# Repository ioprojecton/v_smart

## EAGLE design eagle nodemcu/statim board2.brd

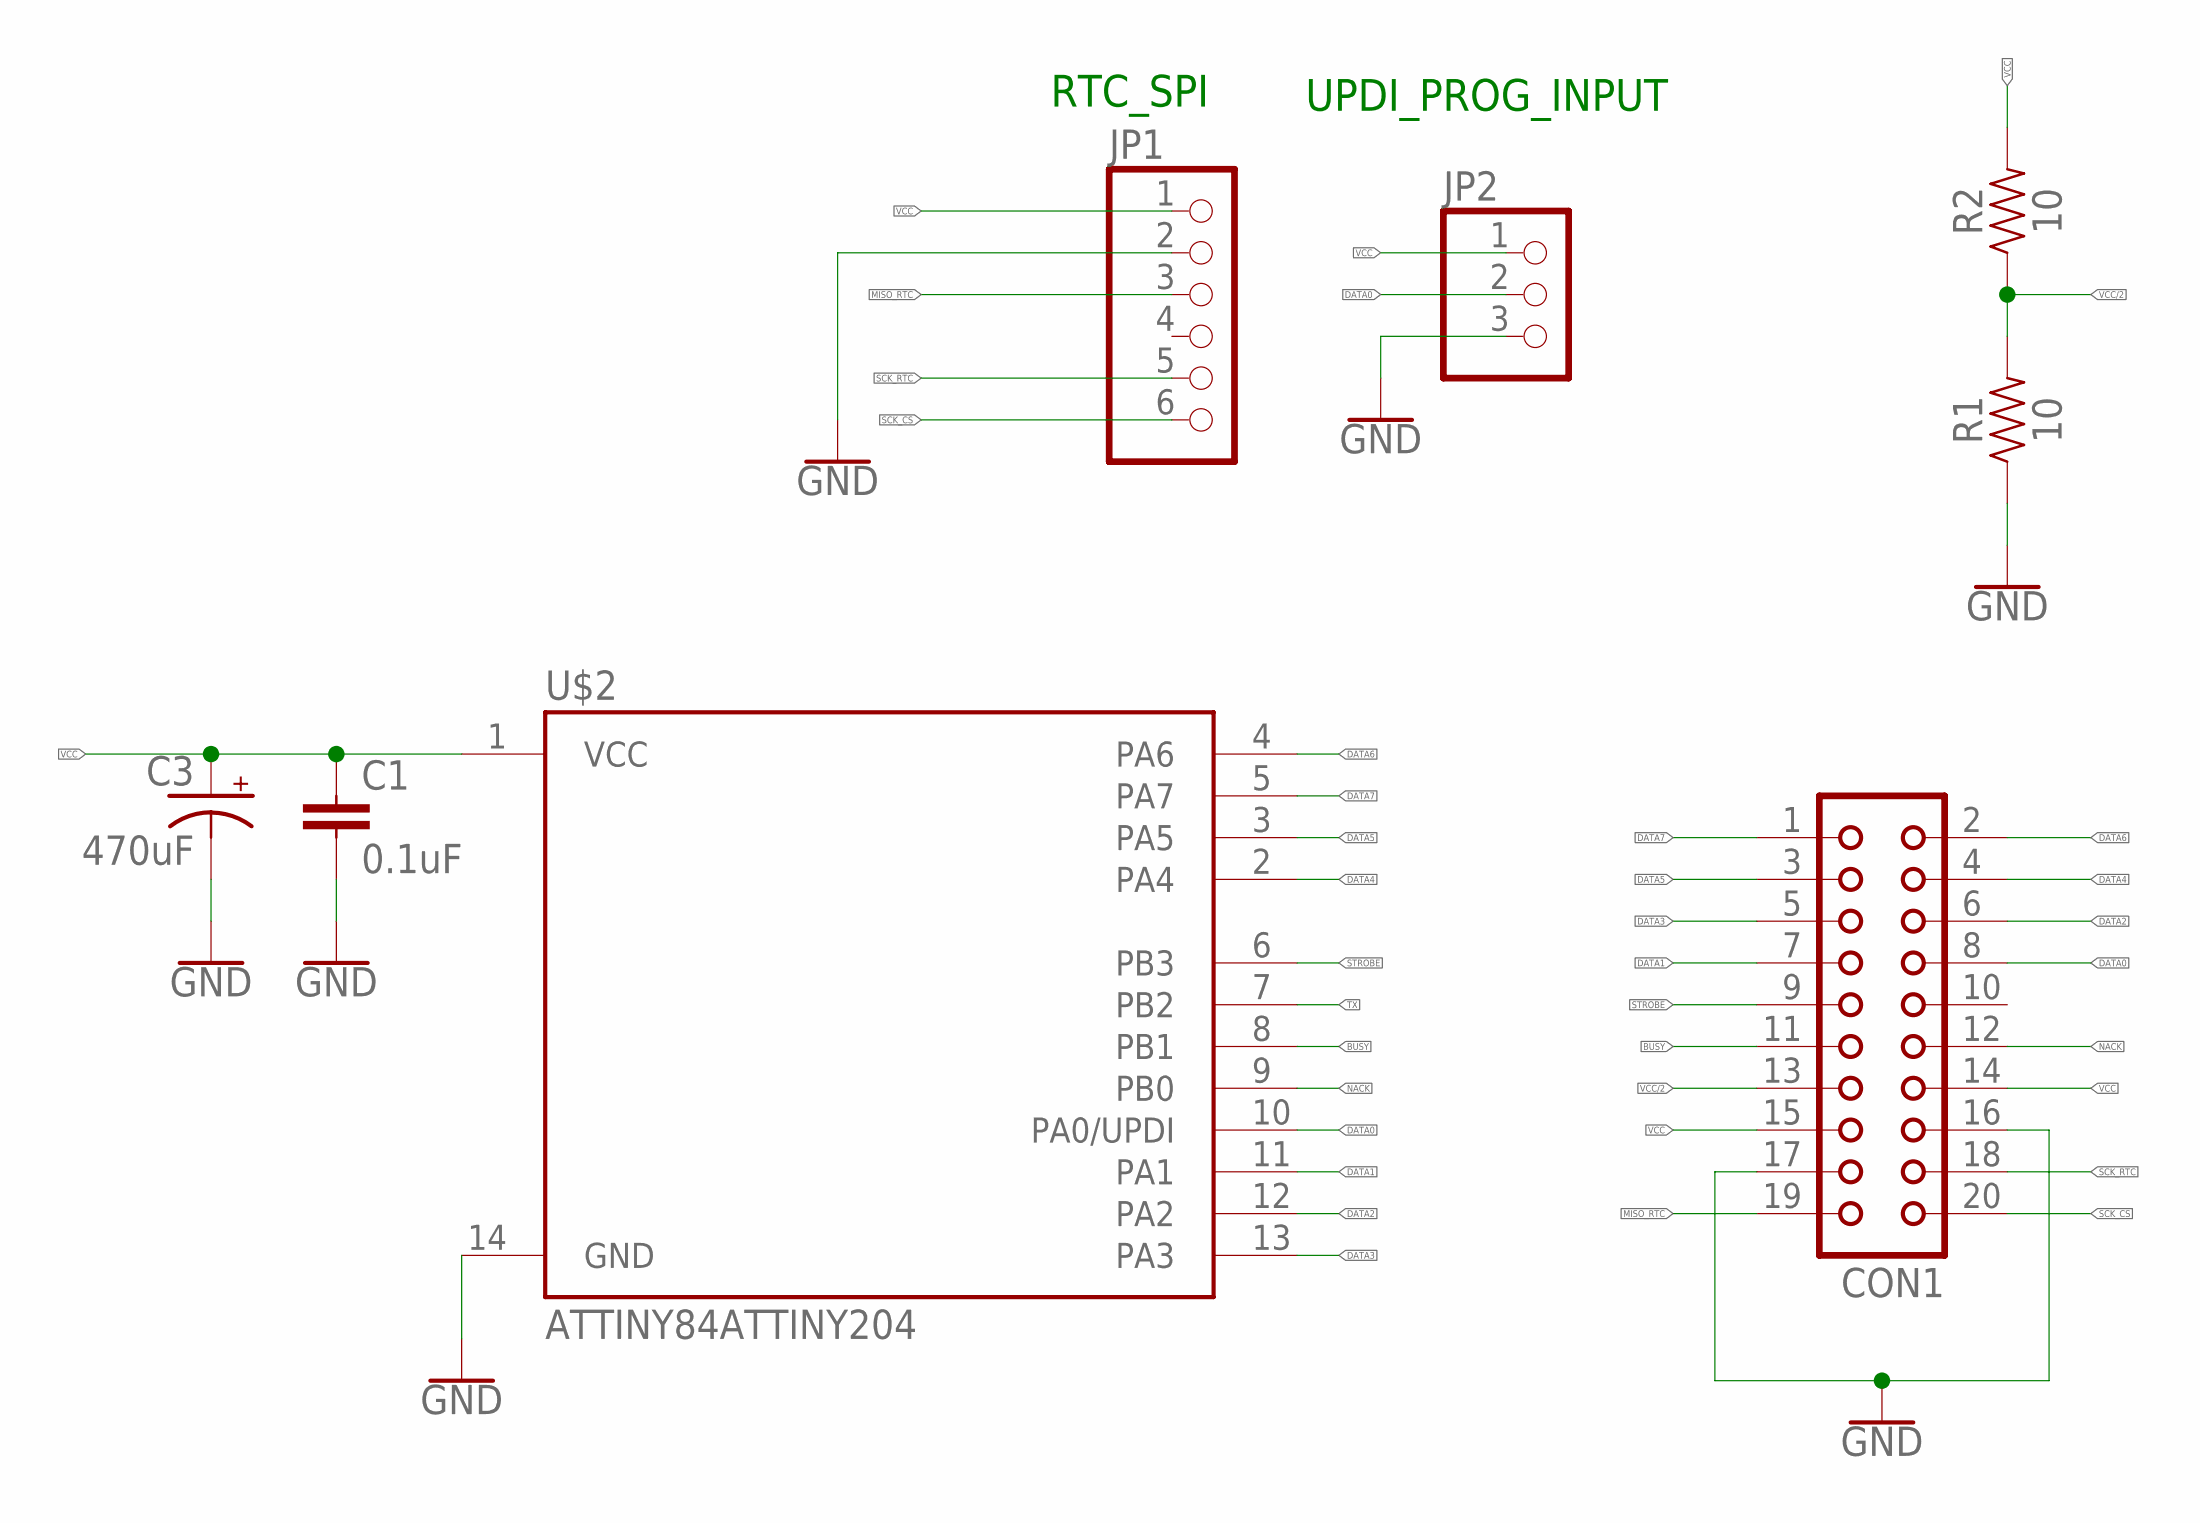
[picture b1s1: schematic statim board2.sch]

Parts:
C1: 0.1uF; 1206
C3: 470uF; PANASONIC_G
CON1: CON20
JP1: PINHD-1X6; 1X06
JP2: PINHD-1X3; 1X03
R1, R2: 10; 1206
U$2: ATTINY84ATTINY204; SO14

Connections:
BUSY: CON1.11, U$2.8 (PB1)
DATA0: CON1.8, JP2.2, U$2.10 (PA0/UPDI)
DATA1: CON1.7, U$2.11 (PA1)
DATA2: CON1.6, U$2.12 (PA2)
DATA3: CON1.5, U$2.13 (PA3)
DATA4: CON1.4, U$2.2 (PA4)
DATA5: CON1.3, U$2.3 (PA5)
DATA6: CON1.2, U$2.4 (PA6)
DATA7: CON1.1, U$2.5 (PA7)
GND: C1.2, C3.-, CON1.16, CON1.17, JP1.2, JP2.3, R1.1, U$2.14 (GND)
MISO_RTC: CON1.19, JP1.3
NACK: CON1.12, U$2.9 (PB0)
SCK_CS: CON1.20, JP1.6
SCK_RTC: CON1.18, JP1.5
STROBE: CON1.9, U$2.6 (PB3)
TX: U$2.7 (PB2)
VCC: C1.1, C3.+, CON1.14, CON1.15, JP1.1, JP2.1, R2.2, U$2.1 (VCC)
VCC/2: CON1.13, R1.2, R2.1

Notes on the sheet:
RTC_SPI
UPDI_PROG_INPUT

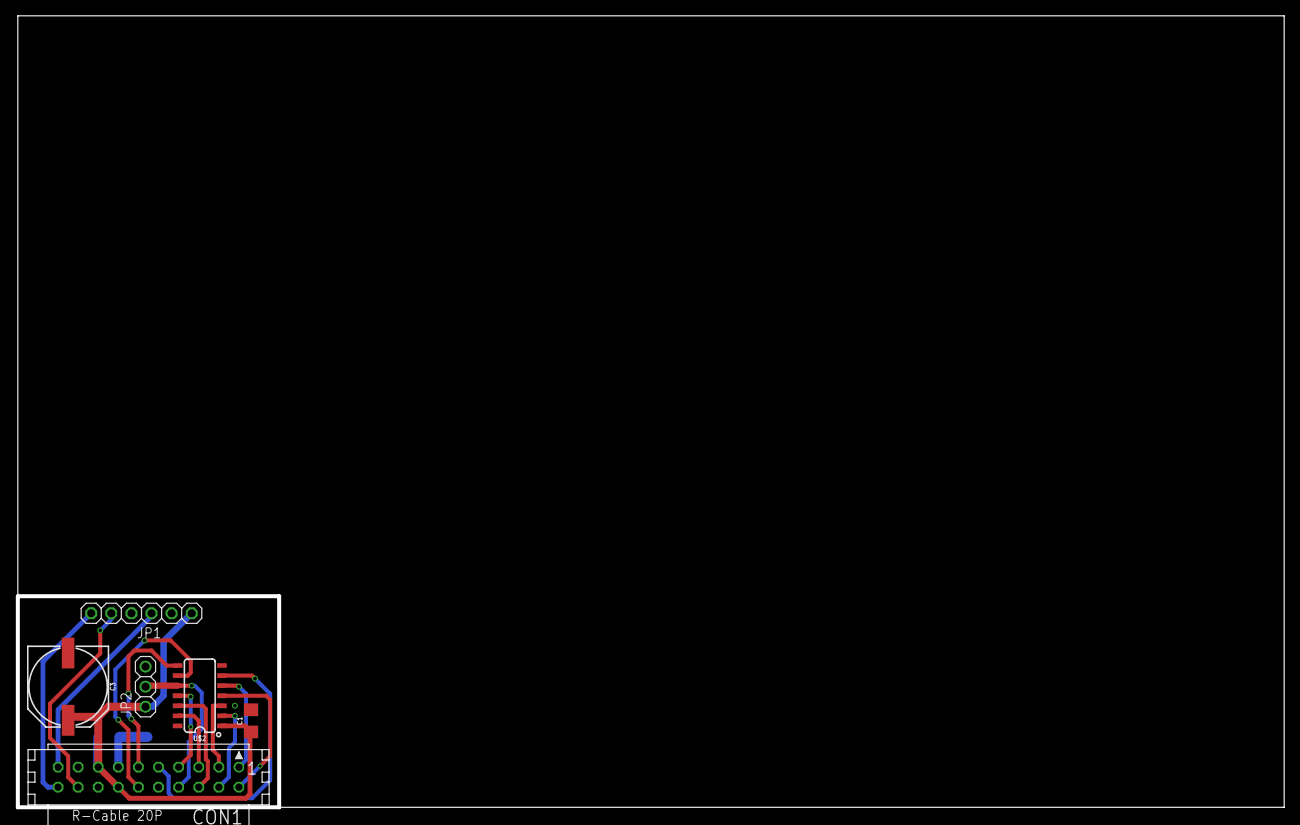
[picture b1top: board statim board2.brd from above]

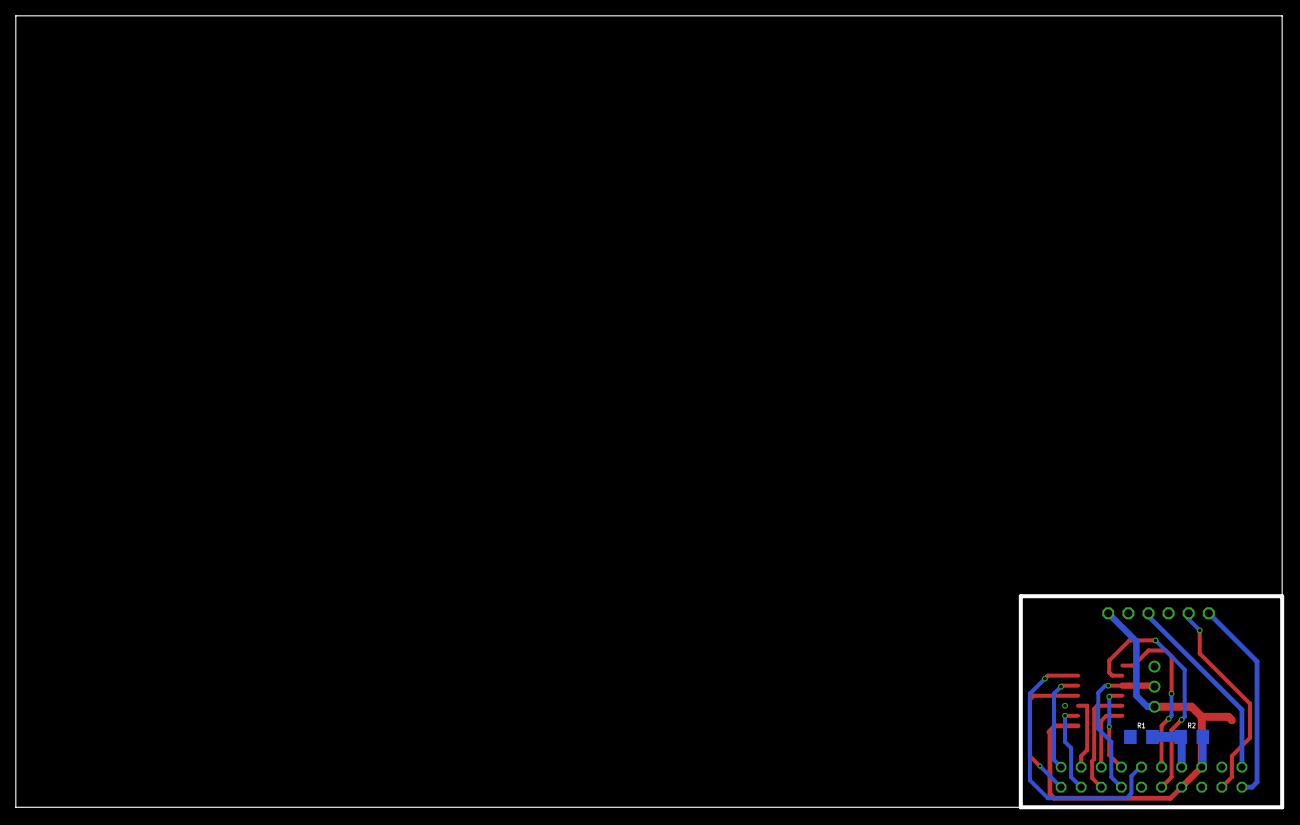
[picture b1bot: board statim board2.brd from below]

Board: 2 copper layers, 160.0 x 100.0 mm, 8 parts (2 on the bottom side), 17 nets.

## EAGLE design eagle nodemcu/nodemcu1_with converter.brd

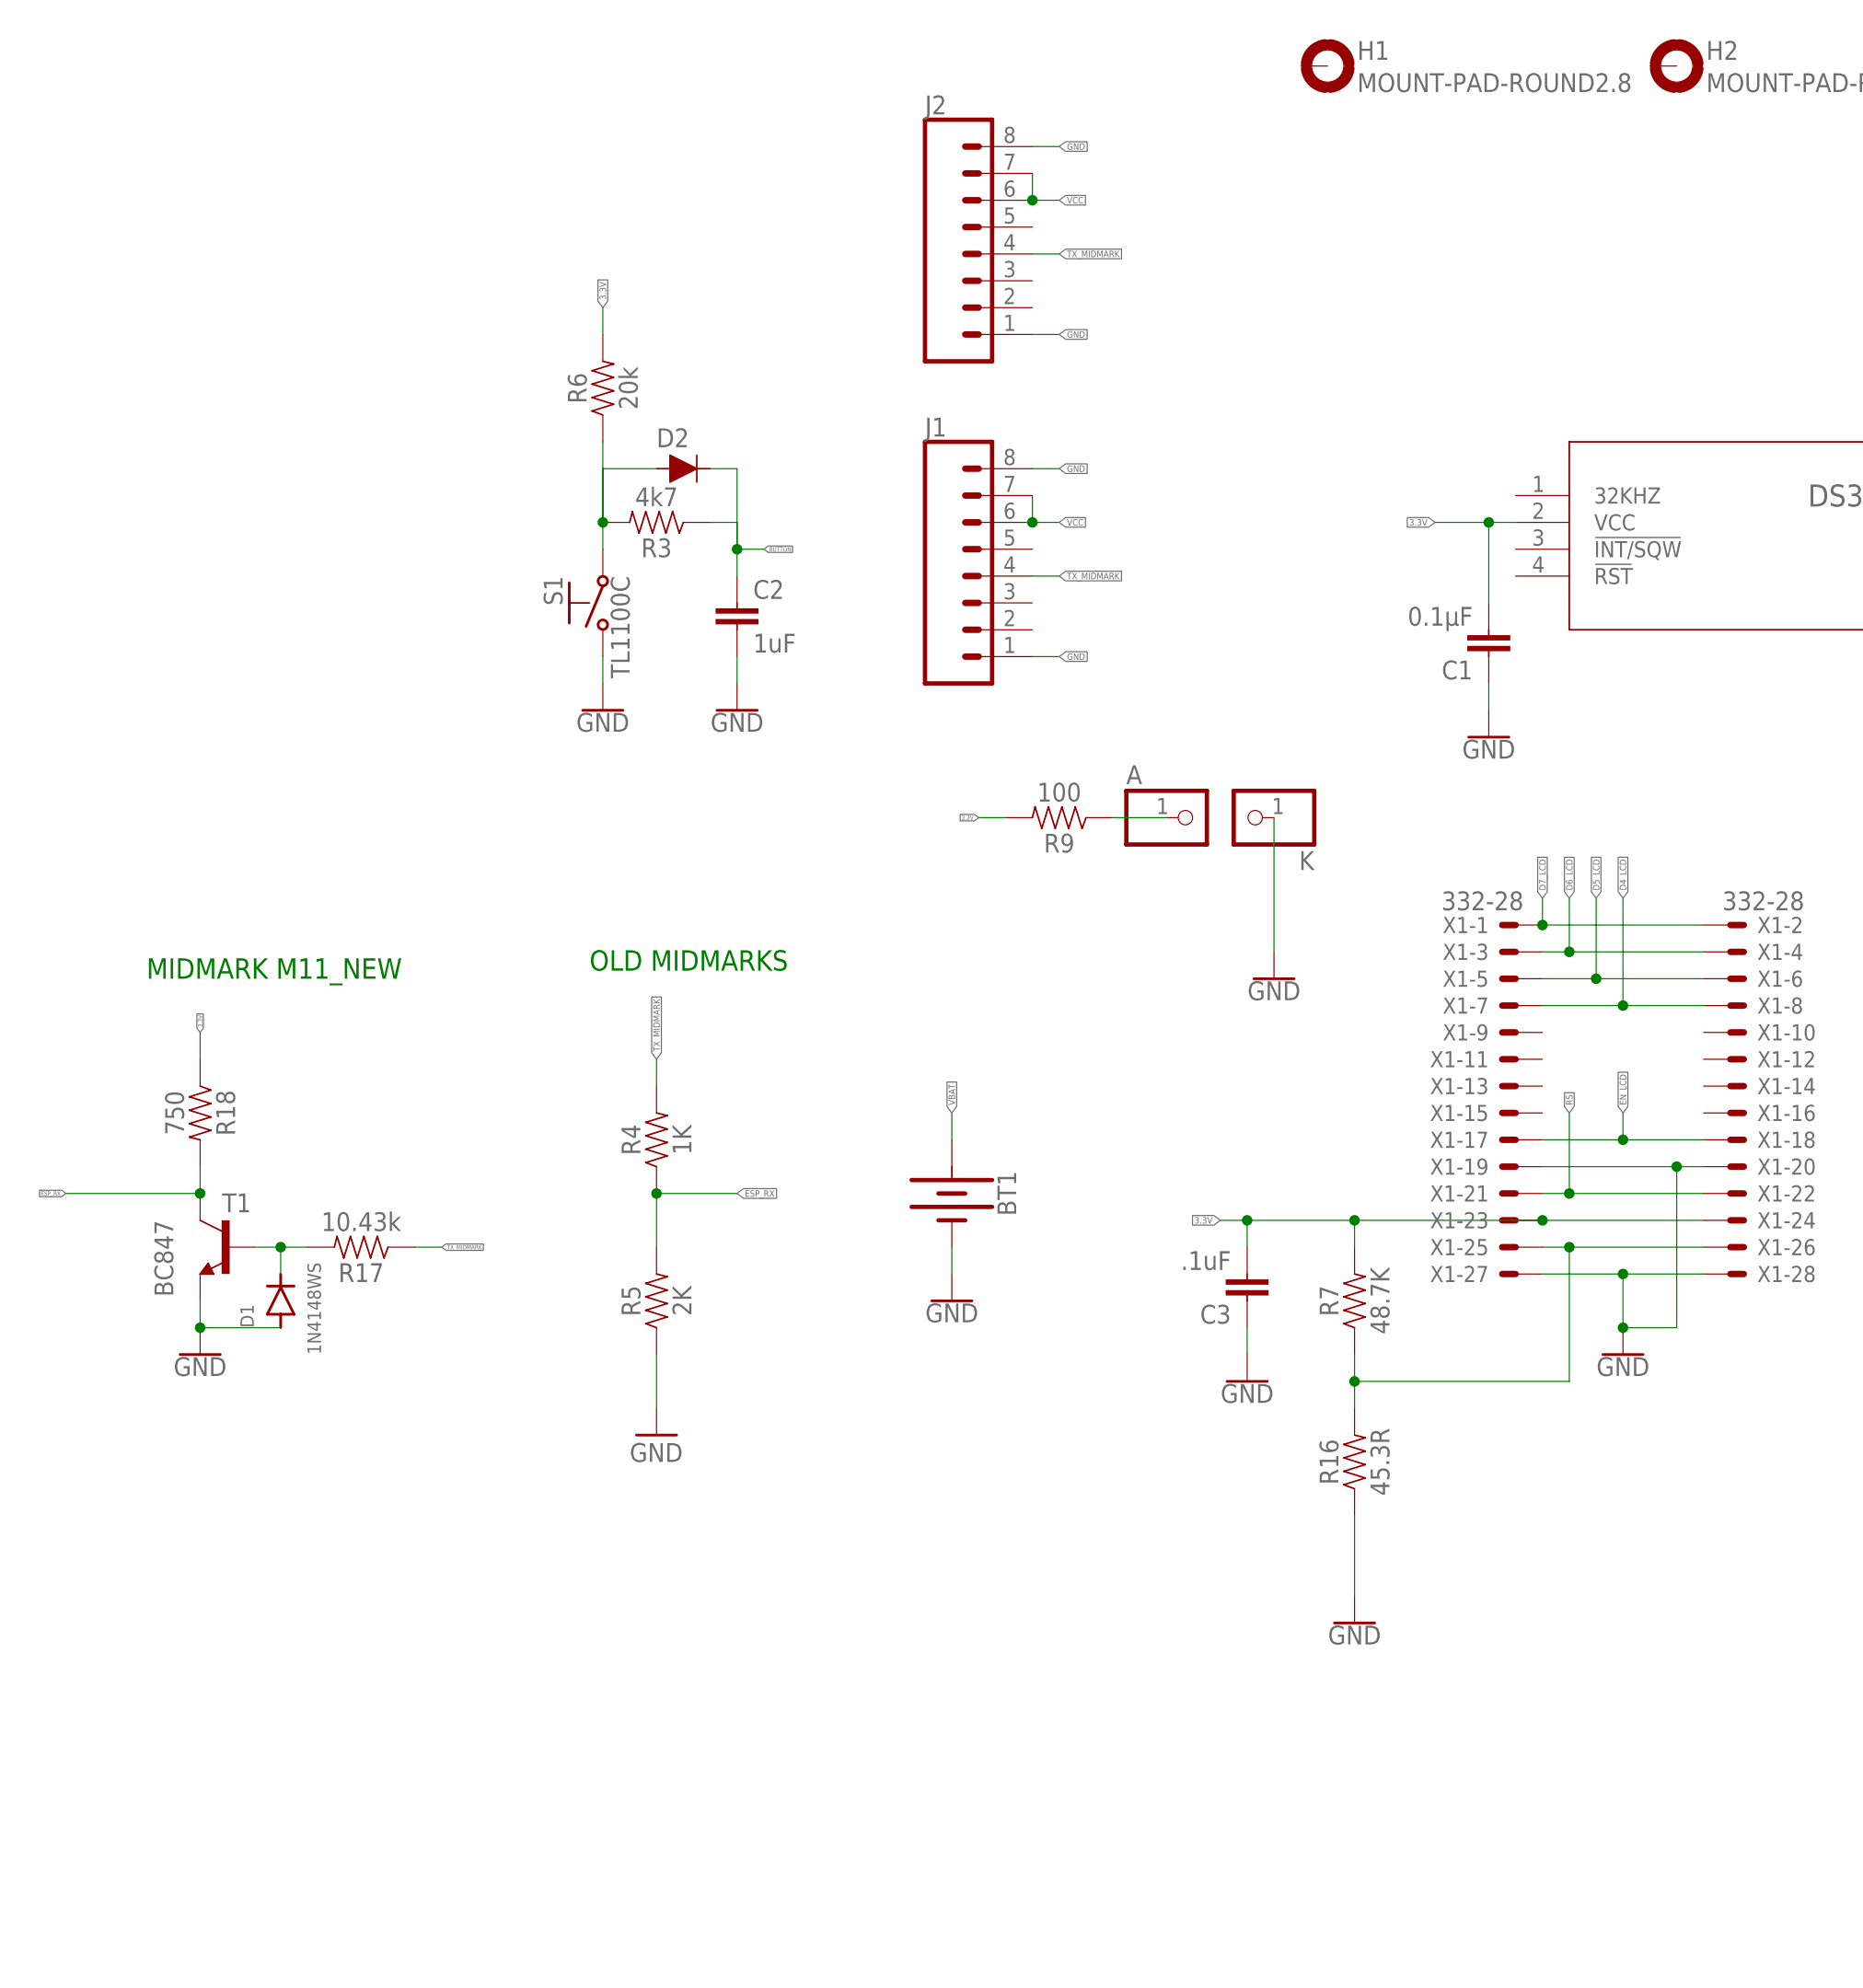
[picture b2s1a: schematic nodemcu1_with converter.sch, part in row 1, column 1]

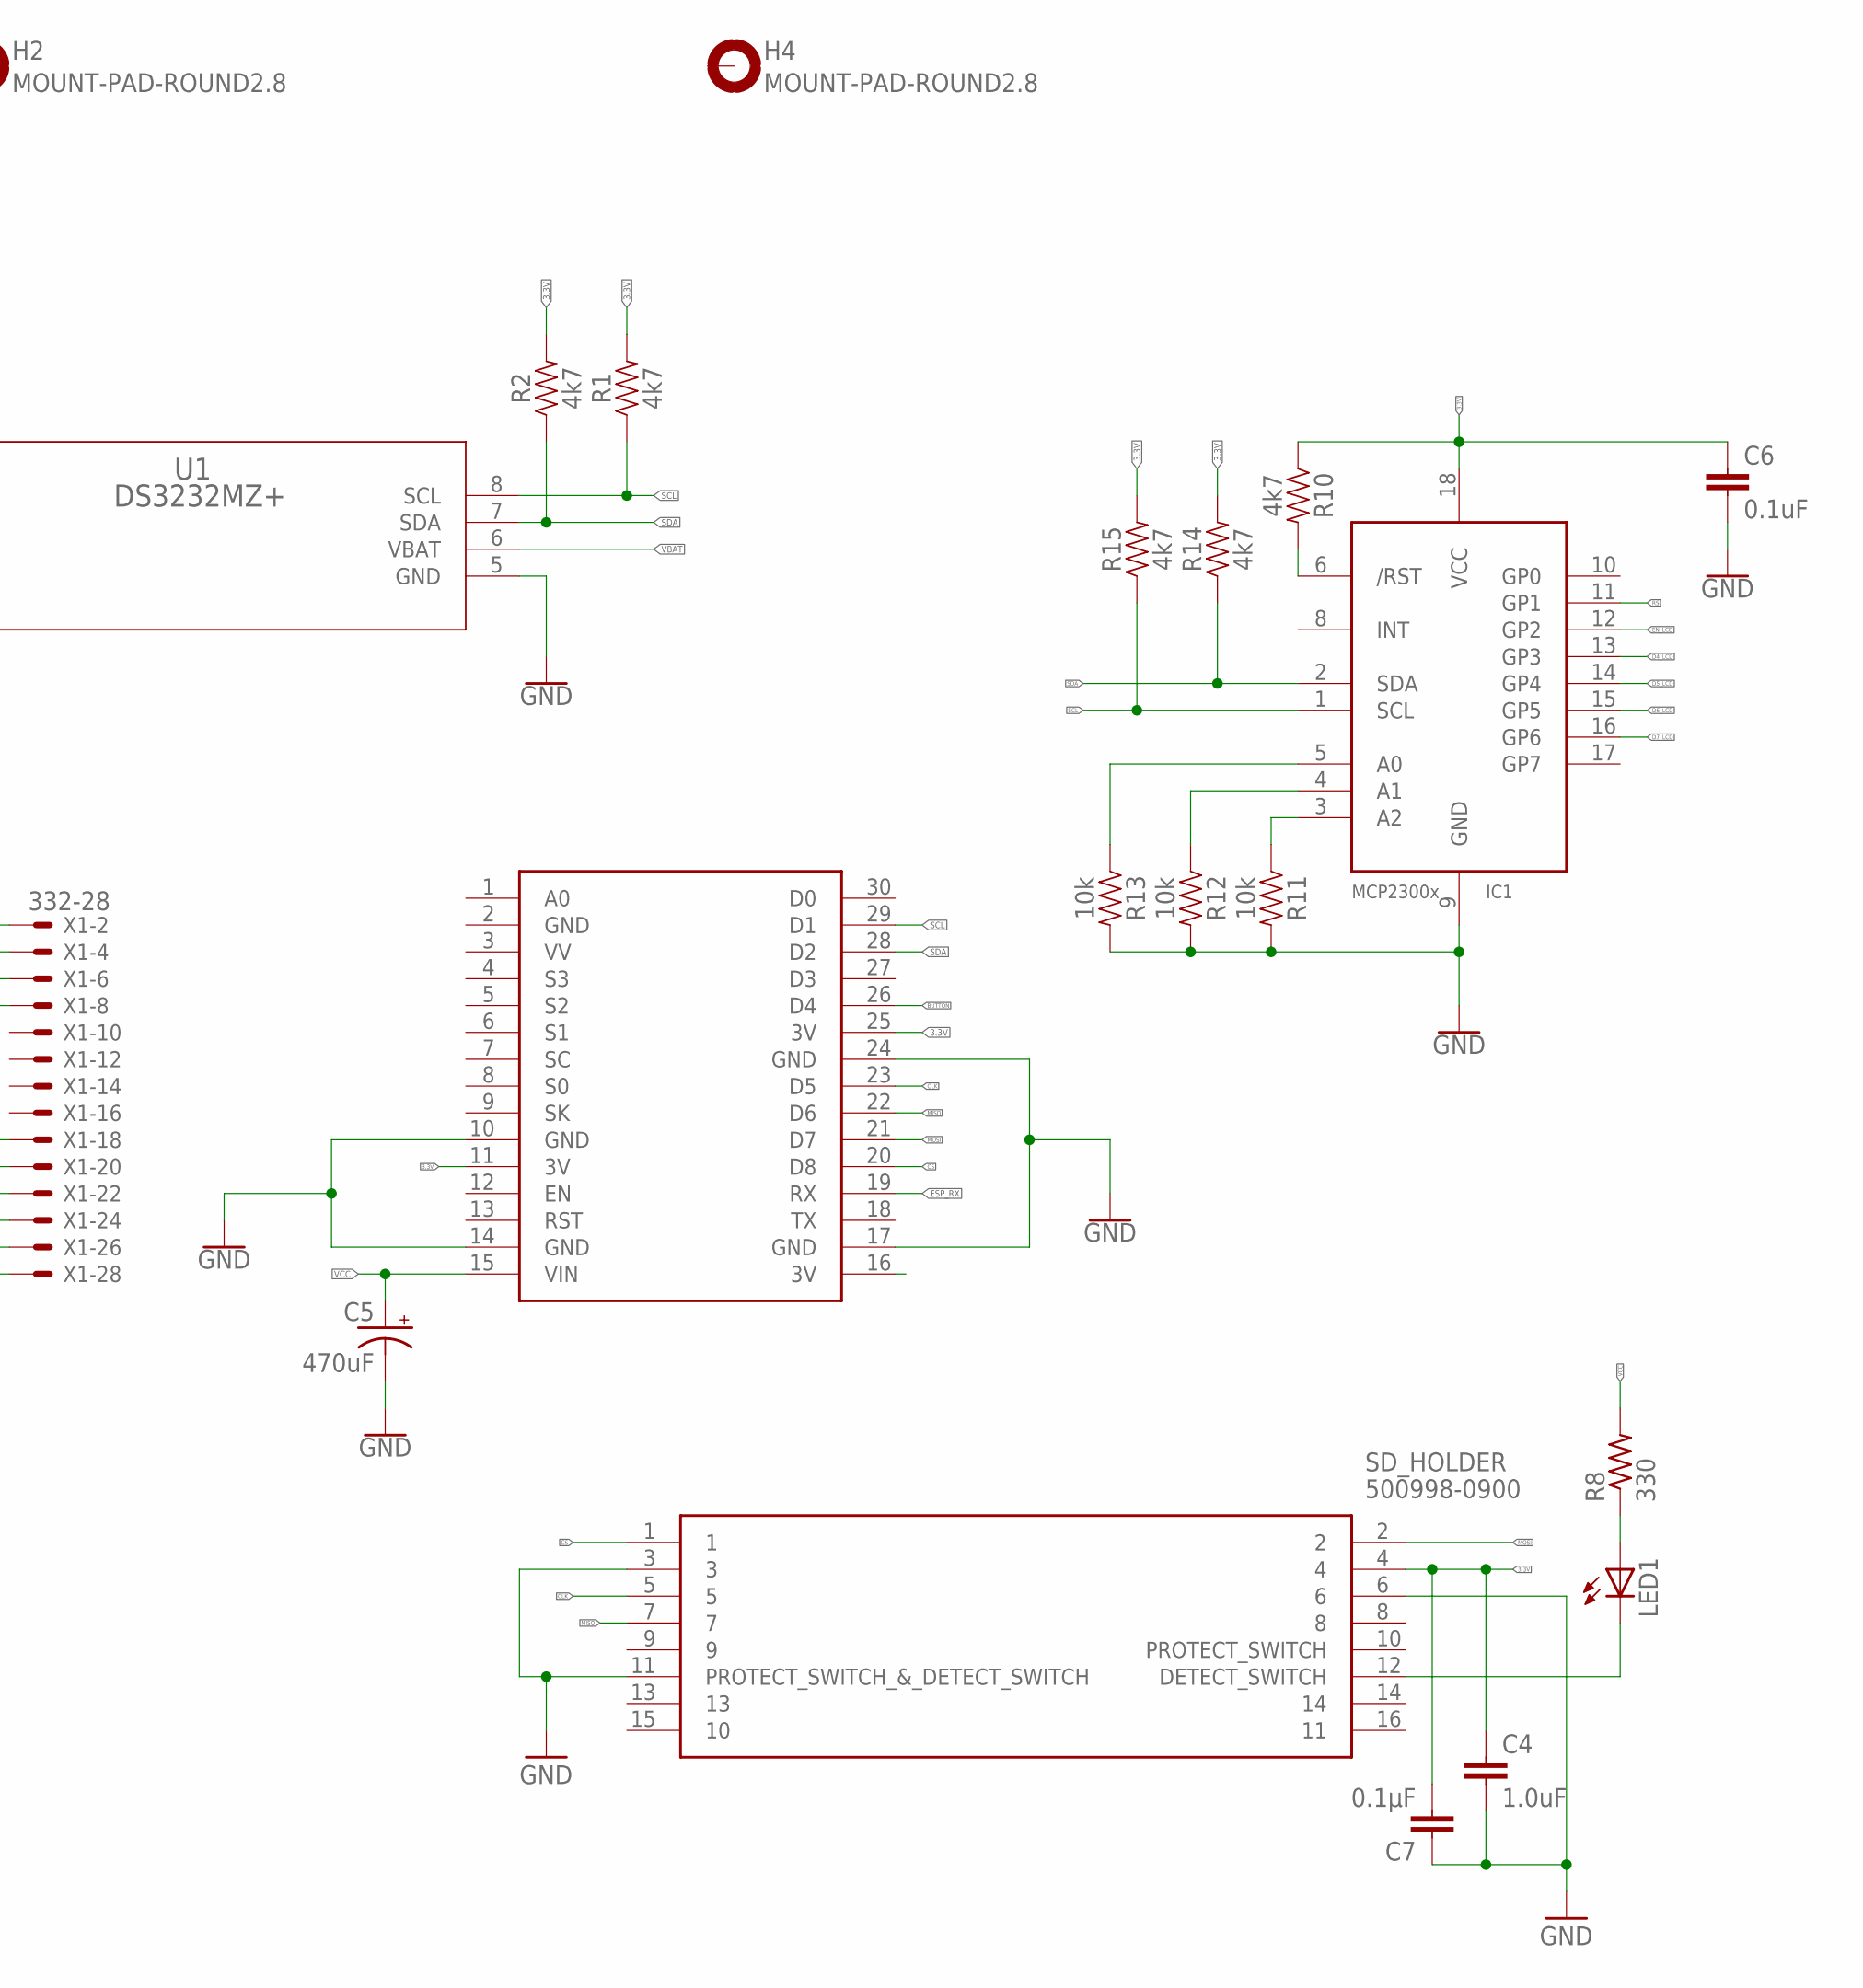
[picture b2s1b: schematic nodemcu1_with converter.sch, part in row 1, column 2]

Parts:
A: PINHD-1X1; 1X01
BT1: BATTERY-20MM_PTH; BATTCOM_20MM_PTH
C1, C7: 0.1µF; 0805
C2: 1uF; 0805
C3: .1uF; 0805
C4: 1.0uF; 1206
C5: 470uF; NIC_10X10.5_CAP
C6: 0.1uF; 0805
D1: 1N4148WS; SOD-323
D2: 1A/50V/1.1V; DIODE-1N4001
H1, H2, H4: MOUNT-PAD-ROUND2.8; 2,8-PAD
IC1: MCP23008/P; DIL18
J1, J2: CONN_08"; 1X08
K: PINHD-1X1; 1X01
LED1: LEDSIDELED; OSRAM-SIDELED
R1, R2, R3, R10, R14, R15: 4k7; 0805
R4: 1K; 0805
R5: 2K; 0805
R6: 20k; 0805
R7: 48.7K; 0805
R8: 330; R0805
R9: 100; 0805
R11, R12, R13: 10k; 0805
R16: 45.3R; 0805
R17: 10.43k; 0805
R18: 750; 0805
S1: TL1100C
SD_HOLDER: 500998-0900; 5009980900
T1: BC847; SOT23
U1: DS3232MZ+; 21-0041B_8
U$1: NODEMCU
X1: 332-28

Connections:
3.3V: C1.2, C3.2, C4.1, C6.1, C7.2, IC1.18 (VCC), R1.2, R2.2, R6.2, R7.2, R9.2, R10.1, R14.2, R15.2, R18.1, SD_HOLDER.4, U1.2 (VCC), U$1.11 (3V), U$1.25 (3V), X1.23, X1.24
BUTTON: C2.1, D2.C, R3.1, U$1.26 (D4)
CLK: SD_HOLDER.5, U$1.23 (D5)
CS: SD_HOLDER.1, U$1.20 (D8)
D4_LCD: IC1.13 (GP3), X1.7, X1.8
D5_LCD: IC1.14 (GP4), X1.5, X1.6
D6_LCD: IC1.15 (GP5), X1.3, X1.4
D7_LCD: IC1.16 (GP6), X1.1, X1.2
EN_LCD: IC1.12 (GP2), X1.17, X1.18
ESP_RX: R4.1, R5.2, R18.2, T1.3 (C), U$1.19 (RX)
GND: BT1.2 (-), C1.1, C2.2, C3.1, C4.2, C5.-, C6.2, C7.1, D1.A, IC1.9 (GND), J1.1, J1.8, J2.1, J2.8, K.1, R5.1, R11.2, R12.2, R13.2, R16.1, S1.2 (S), SD_HOLDER.3, SD_HOLDER.6, SD_HOLDER.11 (PROTECT_SWITCH_&_DETECT_SWITCH), T1.2 (E), U1.5 (GND), U$1.2 (GND), U$1.10 (GND), U$1.14 (GND), U$1.17 (GND), U$1.24 (GND), X1.19, X1.20, X1.27, X1.28
MISO: SD_HOLDER.7, U$1.22 (D6)
MOSI: SD_HOLDER.2, U$1.21 (D7)
unnamed: D2.A, R3.2, R6.1, S1.1
unnamed: A.1, R9.1
unnamed: IC1.6 (/RST), R10.2
unnamed: IC1.3 (A2), R11.1
unnamed: R7.1, R16.2, X1.25, X1.26
unnamed: IC1.4 (A1), R12.1
unnamed: IC1.5 (A0), R13.1
unnamed: D1.C, R17.2, T1.1 (B)
unnamed: LED1.C, SD_HOLDER.12 (DETECT_SWITCH)
unnamed: LED1.A, R8.1
RS: IC1.11 (GP1), X1.21, X1.22
SCL: IC1.1 (SCL), R1.1, R15.1, U1.8 (SCL), U$1.29 (D1)
SDA: IC1.2 (SDA), R2.1, R14.1, U1.7 (SDA), U$1.28 (D2)
TX_MIDMARK: J1.4, J2.4, R4.2, R17.1
VBAT: BT1.1 (+), U1.6 (VBAT)
VCC: C5.+, J1.6, J1.7, J2.6, J2.7, R8.2, U$1.15 (VIN)

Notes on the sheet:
MIDMARK M11_NEW
OLD MIDMARKS

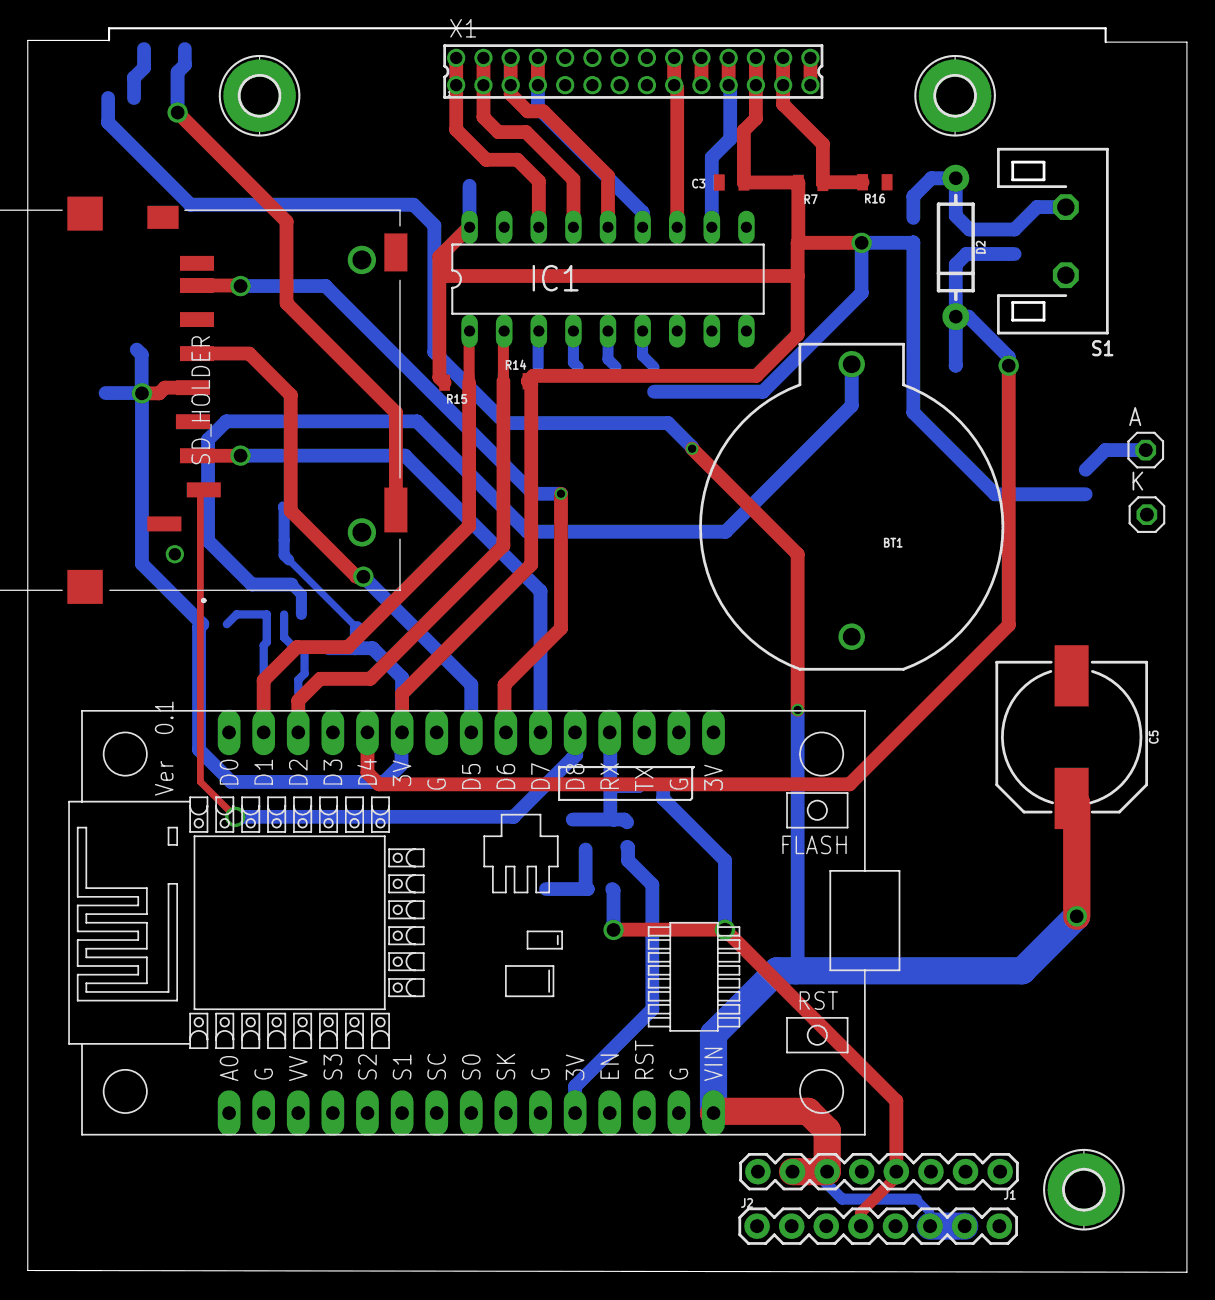
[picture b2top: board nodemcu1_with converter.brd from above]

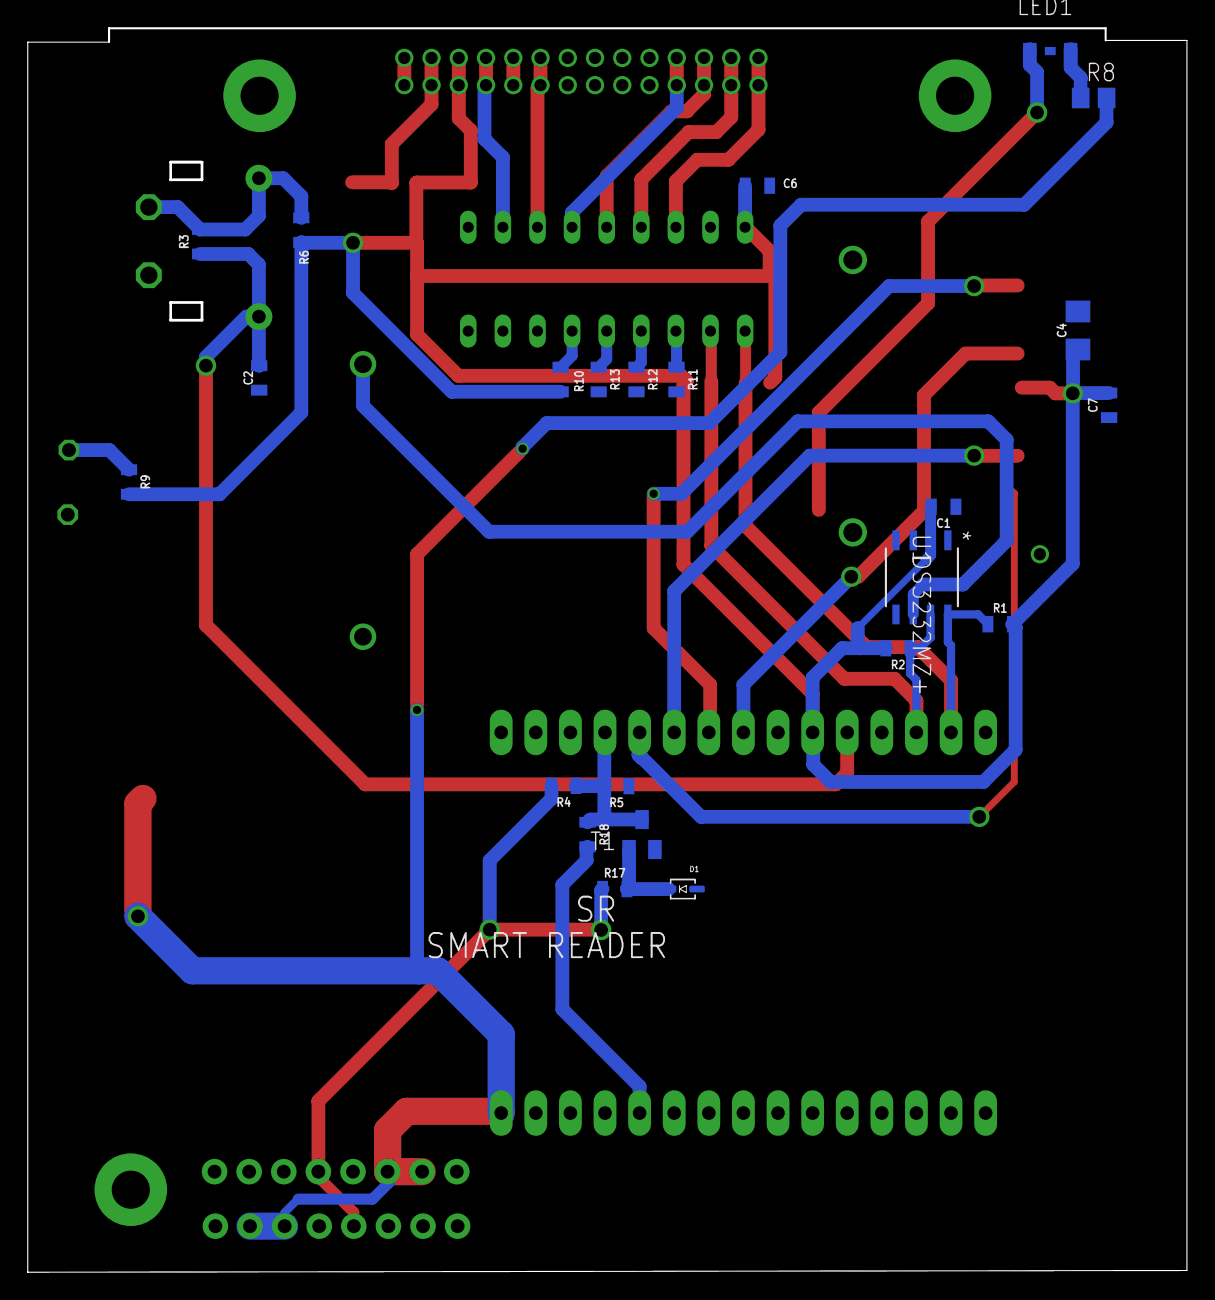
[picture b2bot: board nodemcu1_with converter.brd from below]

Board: 2 copper layers, 85.1 x 91.3 mm, 43 parts (23 on the bottom side), 29 nets.

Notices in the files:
parts and their libraries:
SparkFun-Batteries: Licensing: Creative Commons ShareAlike 4.0 International - https://creativecommons.org/licenses/by-sa/4.0
switch-e-switch: Copyright (C) 2010, Bob Starr
